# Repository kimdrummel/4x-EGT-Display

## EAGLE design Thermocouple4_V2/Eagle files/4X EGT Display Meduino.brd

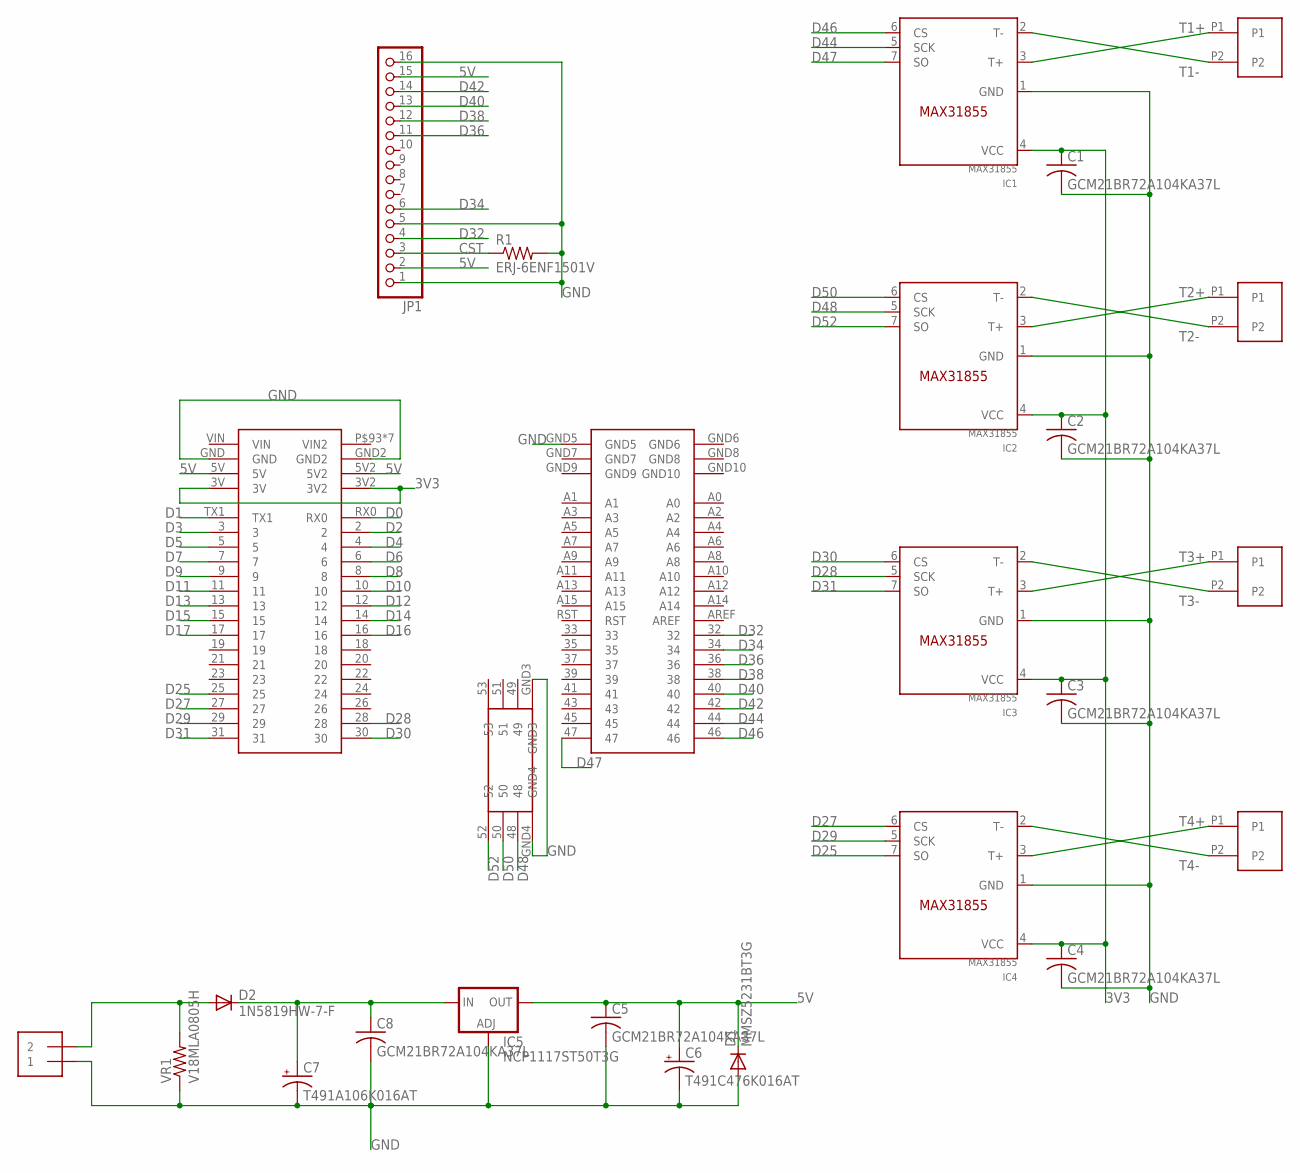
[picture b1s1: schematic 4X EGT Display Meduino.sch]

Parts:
C1, C2, C3, C4, C5, C8: GCM21BR72A104KA37L; C0805K
C6: T491C476K016AT; CT6032
C7: T491A106K016AT; A/3216-18R
D1: MMSZ5231BT3G; SOD123
D2: 1N5819HW-7-F; SOD123
IC1, IC2, IC3, IC4: MAX31855; SOIC8
IC5: NCP1117ST50T3G; SOT223
JP1: PINHD-1X16; 1X16
PWR: 1X2-3.5MM
R1: ERJ-6ENF1501V; R0805
T1, T2, T3, T4: SPTAF_2
U$1: MEDUINO
VR1: V18MLA0805H; R0805

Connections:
3V3: C1.1, C2.1, C3.1, C4.1, IC1.4 (VCC), IC2.4 (VCC), IC3.4 (VCC), IC4.4 (VCC), U$1.3V, U$1.3V2
5V: C5.1, C6.+, D1.C, IC5.4 (OUT), JP1.2, JP1.15, U$1.5V, U$1.5V2
12V: C7.+, C8.1, D2.C, IC5.3 (IN)
12V-RAW: D2.A, PWR.2, VR1.2
CST: JP1.3, R1.1
D0: U$1.RX0
D1: U$1.TX1
D2: U$1.2
D3: U$1.3
D4: U$1.4
D5: U$1.5
D6: U$1.6
D7: U$1.7
D8: U$1.8
D9: U$1.9
D10: U$1.10
D11: U$1.11
D12: U$1.12
D13: U$1.13
D14: U$1.14
D15: U$1.15
D16: U$1.16
D17: U$1.17
D25: IC4.7 (SO), U$1.25
D27: IC4.6 (CS), U$1.27
D28: IC3.5 (SCK), U$1.28
D29: IC4.5 (SCK), U$1.29
D30: IC3.6 (CS), U$1.30
D31: IC3.7 (SO), U$1.31
D32: JP1.4, U$1.32
D34: JP1.6, U$1.34
D36: JP1.11, U$1.36
D38: JP1.12, U$1.38
D40: JP1.13, U$1.40
D42: JP1.14, U$1.42
D44: IC1.5 (SCK), U$1.44
D46: IC1.6 (CS), U$1.46
D47: IC1.7 (SO), U$1.47
D48: IC2.5 (SCK), U$1.48
D50: IC2.6 (CS), U$1.50
D52: IC2.7 (SO), U$1.52
GND: C1.2, C2.2, C3.2, C4.2, C5.2, C6.-, C7.-, C8.2, D1.A, IC1.1 (GND), IC2.1 (GND), IC3.1 (GND), IC4.1 (GND), IC5.1 (ADJ), JP1.1, JP1.5, JP1.16, PWR.1, R1.2, U$1.GND, U$1.GND2, U$1.GND3, U$1.GND4, U$1.GND5, VR1.1
T1+: IC1.3 (T+), T1.P1
T1-: IC1.2 (T-), T1.P2
T2+: IC2.3 (T+), T2.P1
T2-: IC2.2 (T-), T2.P2
T3+: IC3.3 (T+), T3.P1
T3-: IC3.2 (T-), T3.P2
T4+: IC4.3 (T+), T4.P1
T4-: IC4.2 (T-), T4.P2

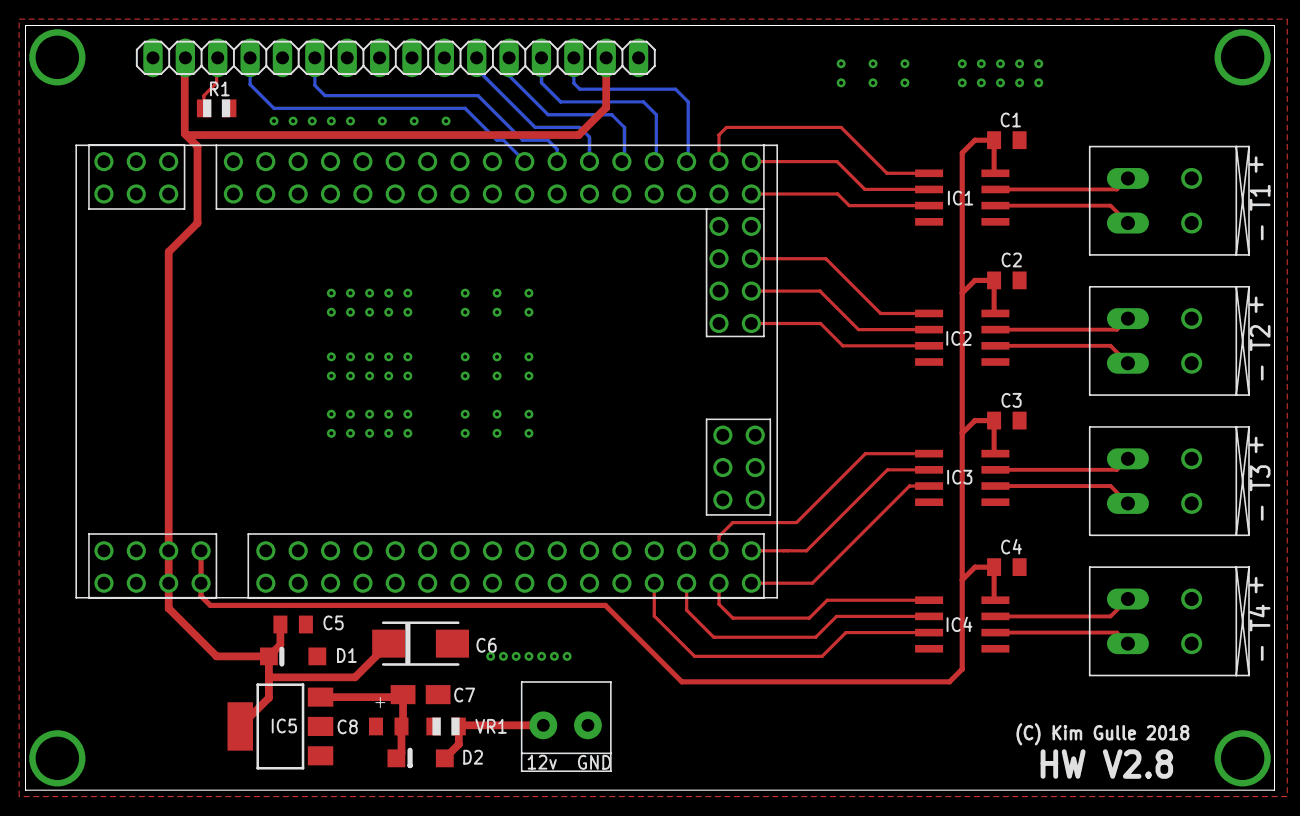
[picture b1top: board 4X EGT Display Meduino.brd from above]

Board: 2 copper layers, 98.0 x 60.0 mm, 24 parts (0 on the bottom side), 32 nets.

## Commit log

2019-07-06 4X EGT Display
    4X EGT Display
